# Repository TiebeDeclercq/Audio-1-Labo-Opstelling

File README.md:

# Audio1-Labo-Opstelling

Complete printplaat met alle schakelingen voor audio 1 en vermogenelektronica @Vives kortrijk.
Met een printbare voet voor betere stabiliteit en geen kortsluiting te krijgen.
Op deze voet wordt er gewerkt met heated inserts (M3) voor het monteren van de print.

De printplaat bevat een Klasse A versterker in twee-traps configuratie met Darlington uitgang. Daarnaast is er een Klasse AB versterker met push-pull configuratie en diode bias die werkt op dual supply spanning.
Voor frequentie-analyse zijn er twee circuits: een BJT common emitter configuratie en een JFET common source configuratie, beide met bypass mogelijkheden. Alle belangrijke signalen zijn toegankelijk via testpunten en connectors.

Het schema is als volgt:

Voor het solderen kan je gebruikmaken van de meegeleverde BOM file, de printplaat is een mix van SMD en TH componenten.

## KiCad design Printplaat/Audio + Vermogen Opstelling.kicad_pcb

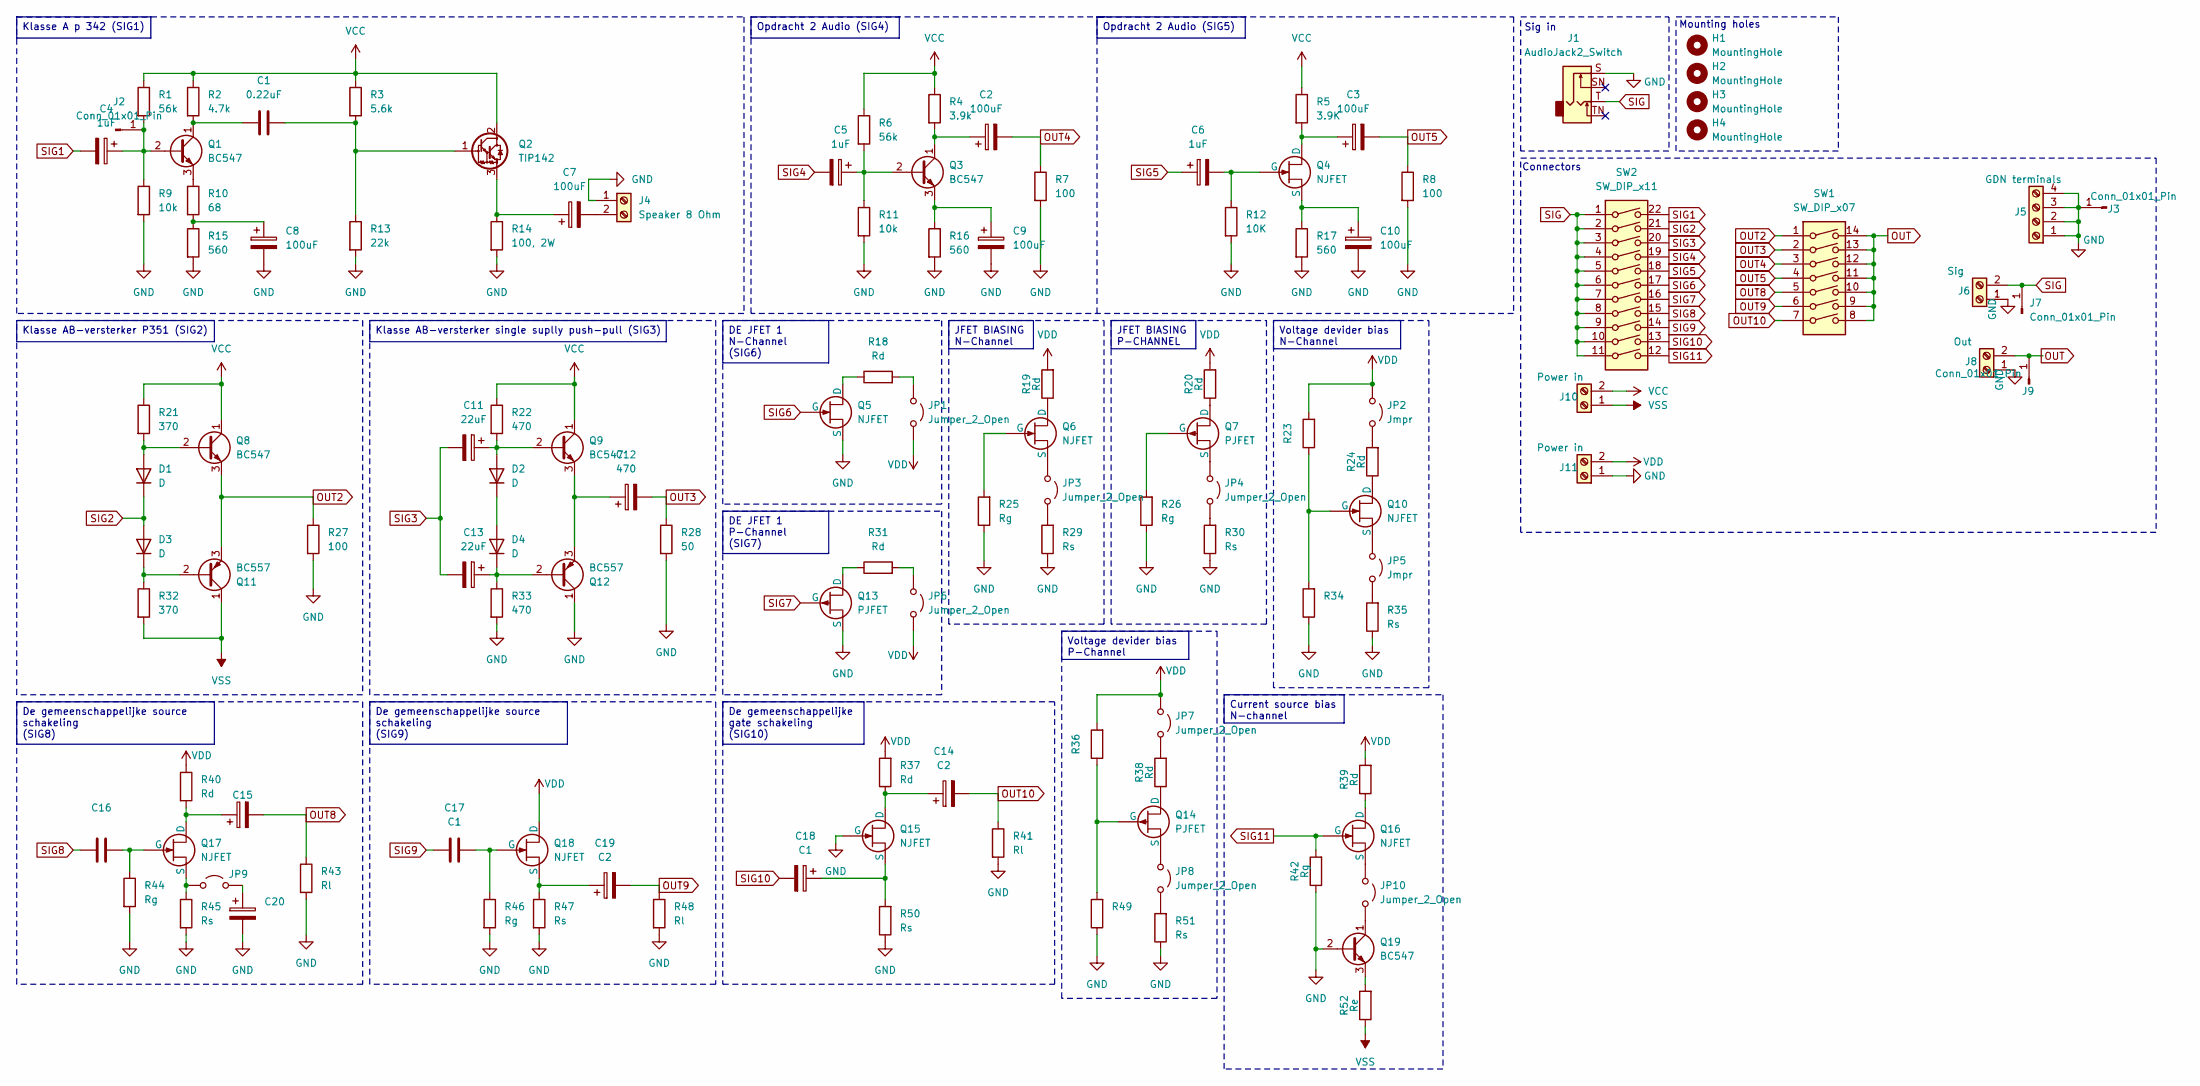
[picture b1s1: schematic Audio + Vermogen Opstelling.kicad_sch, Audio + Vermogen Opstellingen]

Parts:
C1: 0.22uF; C_0805_2012Metric
C2, C3, C9, C10: 100uF; CP_Axial_L11.0mm_D5.0mm_P18.00mm_Horizontal
C4: 1uF; CP_Elec_4x5.4
C5, C6: 1uF; CP_Axial_L11.0mm_D5.0mm_P18.00mm_Horizontal
C7, C8: 100uF; CP_Elec_6.3x5.4
C11, C13: 22uF; CP_Axial_L11.0mm_D5.0mm_P18.00mm_Horizontal
C12: 470; CP_Axial_L11.0mm_D5.0mm_P18.00mm_Horizontal
C14, C19: C2; CP_Axial_L11.0mm_D5.0mm_P18.00mm_Horizontal
C15, C16, C20: CP_Axial_L11.0mm_D5.0mm_P18.00mm_Horizontal
C17, C18: C1; CP_Axial_L11.0mm_D5.0mm_P18.00mm_Horizontal
D1, D2, D3, D4: D; D_DO-15_P15.24mm_Horizontal
H1, H2, H3, H4: MountingHole; MountingHole_3.2mm_M3
J1: AudioJack2_Switch; Jack_3.5mm_KoreanHropartsElec_PJ-320D-4A_Horizontal
J2, J3, J7, J9: Conn_01x01_Pin; PinHeader_1x01_P2.54mm_Vertical
J4: Speaker 8 Ohm; TerminalBlock_Phoenix_MKDS-1,5-2_1x02_P5.00mm_Horizontal
J5: GDN terminals; TerminalBlock_Phoenix_MKDS-1,5-4-5.08_1x04_P5.08mm_Horizont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
J6: Sig; TerminalBlock_Phoenix_MKDS-1,5-2_1x02_P5.00mm_Horizontal
J8: Out; TerminalBlock_Phoenix_MKDS-1,5-2_1x02_P5.00mm_Horizontal
J10, J11: Power in; TerminalBlock_Phoenix_MKDS-1,5-2_1x02_P5.00mm_Horizontal
JP1, JP3, JP4, JP6, JP7, JP8, JP10: Jumper_2_Open; PinHeader_1x02_P2.54mm_Vertical
JP2, JP5: Jmpr; PinHeader_1x02_P2.54mm_Vertical
JP9: PinHeader_1x02_P2.54mm_Vertical
Q1, Q3, Q8, Q9, Q19: BC547; TO-92_Inline
Q2: TIP142; TO-220-3_Horizontal_TabDown
Q4, Q5, Q6, Q10, Q15, Q16, Q17, Q18: NJFET; TRANS_J109
Q7, Q13, Q14: PJFET; SOT23
Q11, Q12: BC557; TO-92_Inline
R1: 56k; R_0805_2012Metric_Pad1.20x1.40mm_HandSolder
R2: 4.7k; R_0805_2012Metric_Pad1.20x1.40mm_HandSolder
R3: 5.6k; R_0805_2012Metric_Pad1.20x1.40mm_HandSolder
R4: 3.9k; R_Axial_DIN0207_L6.3mm_D2.5mm_P10.16mm_Horizontal
R5: 3.9K; R_Axial_DIN0207_L6.3mm_D2.5mm_P10.16mm_Horizontal
R6: 56k; R_Axial_DIN0207_L6.3mm_D2.5mm_P10.16mm_Horizontal
R7, R8, R27: 100; R_Axial_DIN0207_L6.3mm_D2.5mm_P10.16mm_Horizontal
R9: 10k; R_0805_2012Metric_Pad1.20x1.40mm_HandSolder
R10: 68; R_0805_2012Metric_Pad1.20x1.40mm_HandSolder
R11: 10k; R_Axial_DIN0207_L6.3mm_D2.5mm_P10.16mm_Horizontal
R12: 10K; R_Axial_DIN0207_L6.3mm_D2.5mm_P10.16mm_Horizontal
R13: 22k; R_0805_2012Metric_Pad1.20x1.40mm_HandSolder
R14: 100, 2W; R_2512_6332Metric_Pad1.40x3.35mm_HandSolder
R15: 560; R_0805_2012Metric_Pad1.20x1.40mm_HandSolder
R16, R17: 560; R_Axial_DIN0207_L6.3mm_D2.5mm_P10.16mm_Horizontal
R18, R19, R20, R24, R31, R37, R38, R39, R40: Rd; R_Axial_DIN0207_L6.3mm_D2.5mm_P10.16mm_Horizontal
R21, R32: 370; R_Axial_DIN0207_L6.3mm_D2.5mm_P10.16mm_Horizontal
R22, R33: 470; R_Axial_DIN0207_L6.3mm_D2.5mm_P10.16mm_Horizontal
R23, R34, R36, R49: R_Axial_DIN0207_L6.3mm_D2.5mm_P10.16mm_Horizontal
R25, R26, R42, R44, R46: Rg; R_Axial_DIN0207_L6.3mm_D2.5mm_P10.16mm_Horizontal
R28: 50; R_Axial_DIN0207_L6.3mm_D2.5mm_P10.16mm_Horizontal
R29, R30, R35, R45, R47, R50, R51: Rs; R_Axial_DIN0207_L6.3mm_D2.5mm_P10.16mm_Horizontal
R41, R43, R48: Rl; R_Axial_DIN0207_L6.3mm_D2.5mm_P10.16mm_Horizontal
R52: Re; R_Axial_DIN0207_L6.3mm_D2.5mm_P10.16mm_Horizontal
SW1: SW_DIP_x07; SW_DIP_SPSTx07_Slide_9.78x19.96mm_W7.62mm_P2.54mm
SW2: SW_DIP_x11; SW_DIP_SPSTx11_Slide_9.78x30.12mm_W7.62mm_P2.54mm

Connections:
GND: C8.2, C9.2, C10.2, C20.2, J1.S, J3.1, J4.1, J5.1, J5.2, J5.3, J5.4, J6.1, J8.1, J11.1, Q5.3 (S), Q12.1 (C), Q13.3 (S), Q15.2 (G), Q19.2 (B), R7.2, R8.2, R9.2, R11.2, R12.2, R13.2, R14.2, R15.2, R16.2, R17.2, R25.1, R26.1, R27.2, R28.2, R29.1, R30.1, R33.2, R34.1, R35.1, R41.2, R42.1, R43.2, R44.2, R45.2, R46.2, R47.2, R48.2, R49.1, R50.1, R51.1
unnamed: C8.1, R10.2, R15.1
unnamed: D1.2 (A), Q8.2 (B), R21.2
unnamed: C11.1, D2.2 (A), Q9.2 (B), R22.2
unnamed: D2.1 (K), D4.2 (A)
unnamed: D3.1 (K), Q11.2 (B), R32.1
unnamed: C13.1, D4.1 (K), Q12.2 (B), R33.1
unnamed: C4.1, J2.1, Q1.2 (B), R1.2, R9.1
unnamed: C7.2, J4.2
unnamed: JP1.1 (A), R18.2
unnamed: JP2.2 (B), R24.2
unnamed: JP3.1 (A), Q6.3 (S)
unnamed: JP3.2 (B), R29.2
unnamed: JP4.1 (A), Q7.3 (S)
unnamed: JP4.2 (B), R30.2
unnamed: JP5.1 (A), Q10.3 (S)
unnamed: JP5.2 (B), R35.2
unnamed: JP6.1 (A), R31.2
unnamed: JP7.2 (B), R38.2
unnamed: JP8.1 (A), Q14.3 (S)
unnamed: JP8.2 (B), R51.2
unnamed: JP9.1 (A), Q17.3 (S), R45.1
unnamed: C20.1, JP9.2 (B)
unnamed: JP10.1 (A), Q16.3 (S)
unnamed: JP10.2 (B), Q19.1 (C)
unnamed: C1.1, Q1.1 (C), R2.2
unnamed: Q1.3 (E), R10.1
unnamed: C1.2, Q2.1 (B), R3.2, R13.1
unnamed: C7.1, Q2.3 (E), R14.1
unnamed: C5.1, Q3.2 (B), R6.2, R11.1
unnamed: C2.1, Q3.1 (C), R4.2
unnamed: C9.1, Q3.3 (E), R16.1
unnamed: C3.1, Q4.1 (D), R5.2
unnamed: C6.2, Q4.2 (G), R12.1
unnamed: C10.1, Q4.3 (S), R17.1
unnamed: Q5.1 (D), R18.1
unnamed: Q6.1 (D), R19.1
unnamed: Q6.2 (G), R25.2
unnamed: Q7.1 (D), R20.1
unnamed: Q7.2 (G), R26.2
unnamed: Q10.1 (D), R24.1
unnamed: Q10.2 (G), R23.1, R34.2
unnamed: C12.1, Q9.3 (E), Q12.3 (E)
unnamed: Q13.1 (D), R31.1
unnamed: Q14.1 (D), R38.1
unnamed: Q14.2 (G), R36.1, R49.2
unnamed: C14.1, Q15.1 (D), R37.1
unnamed: C18.1, Q15.3 (S), R50.2
unnamed: Q16.1 (D), R39.1
unnamed: C15.1, Q17.1 (D), R40.2
unnamed: C16.2, Q17.2 (G), R44.1
unnamed: C17.2, Q18.2 (G), R46.1
unnamed: C19.1, Q18.3 (S), R47.1
unnamed: Q19.3 (E), R52.2
OUT: J8.2, J9.1, SW1.8, SW1.9, SW1.10, SW1.11, SW1.12, SW1.13, SW1.14
OUT2: Q8.3 (E), Q11.3 (E), R27.1, SW1.1
OUT3: C12.2, R28.1, SW1.2
OUT4: C2.2, R7.1, SW1.3
OUT5: C3.2, R8.1, SW1.4
OUT8: C15.2, R43.1, SW1.5
OUT9: C19.2, R48.1, SW1.6
OUT10: C14.2, R41.1, SW1.7
SIG: J1.T, J6.2, J7.1, SW2.1, SW2.2, SW2.3, SW2.4, SW2.5, SW2.6, SW2.7, SW2.8, SW2.9, SW2.10, SW2.11
SIG1: C4.2, SW2.22
SIG2: D1.1 (K), D3.2 (A), SW2.21
SIG3: C11.2, C13.2, SW2.20
SIG4: C5.2, SW2.19
SIG5: C6.1, SW2.18
SIG6: Q5.2 (G), SW2.17
SIG7: Q13.2 (G), SW2.16
SIG8: C16.1, SW2.15
SIG9: C17.1, SW2.14
SIG10: C18.2, SW2.13
SIG11: Q16.2 (G), R42.2, SW2.12
VCC: J10.2, Q2.2 (C), Q8.1 (C), Q9.1 (C), R1.1, R2.1, R3.1, R4.1, R5.1, R6.1, R21.1, R22.1
VDD: J11.2, JP1.2 (B), JP2.1 (A), JP6.2 (B), JP7.1 (A), Q18.1 (D), R19.2, R20.2, R23.2, R36.2, R37.2, R39.2, R40.1
VSS: J10.1, Q11.1 (C), R32.2, R52.1

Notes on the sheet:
Sig in
Connectors
Mounting holes
DE JFET 1 N-Channel (SIG6)
Klasse AB-versterker single suplly push-pull (SIG3)
De gemeenschappelijke source schakeling (SIG9)
Current source bias N-channel
DE JFET 1 P-Channel (SIG7)
Opdracht 2 Audio (SIG5)
Opdracht 2 Audio (SIG4)
Klasse AB-versterker P351 (SIG2)
De gemeenschappelijke source schakeling (SIG8)
JFET BIASING N-Channel
Voltage devider bias N-Channel
Voltage devider bias P-Channel
Klasse A p 342 (SIG1)
JFET BIASING P-CHANNEL
De gemeenschappelijke gate schakeling (SIG10)

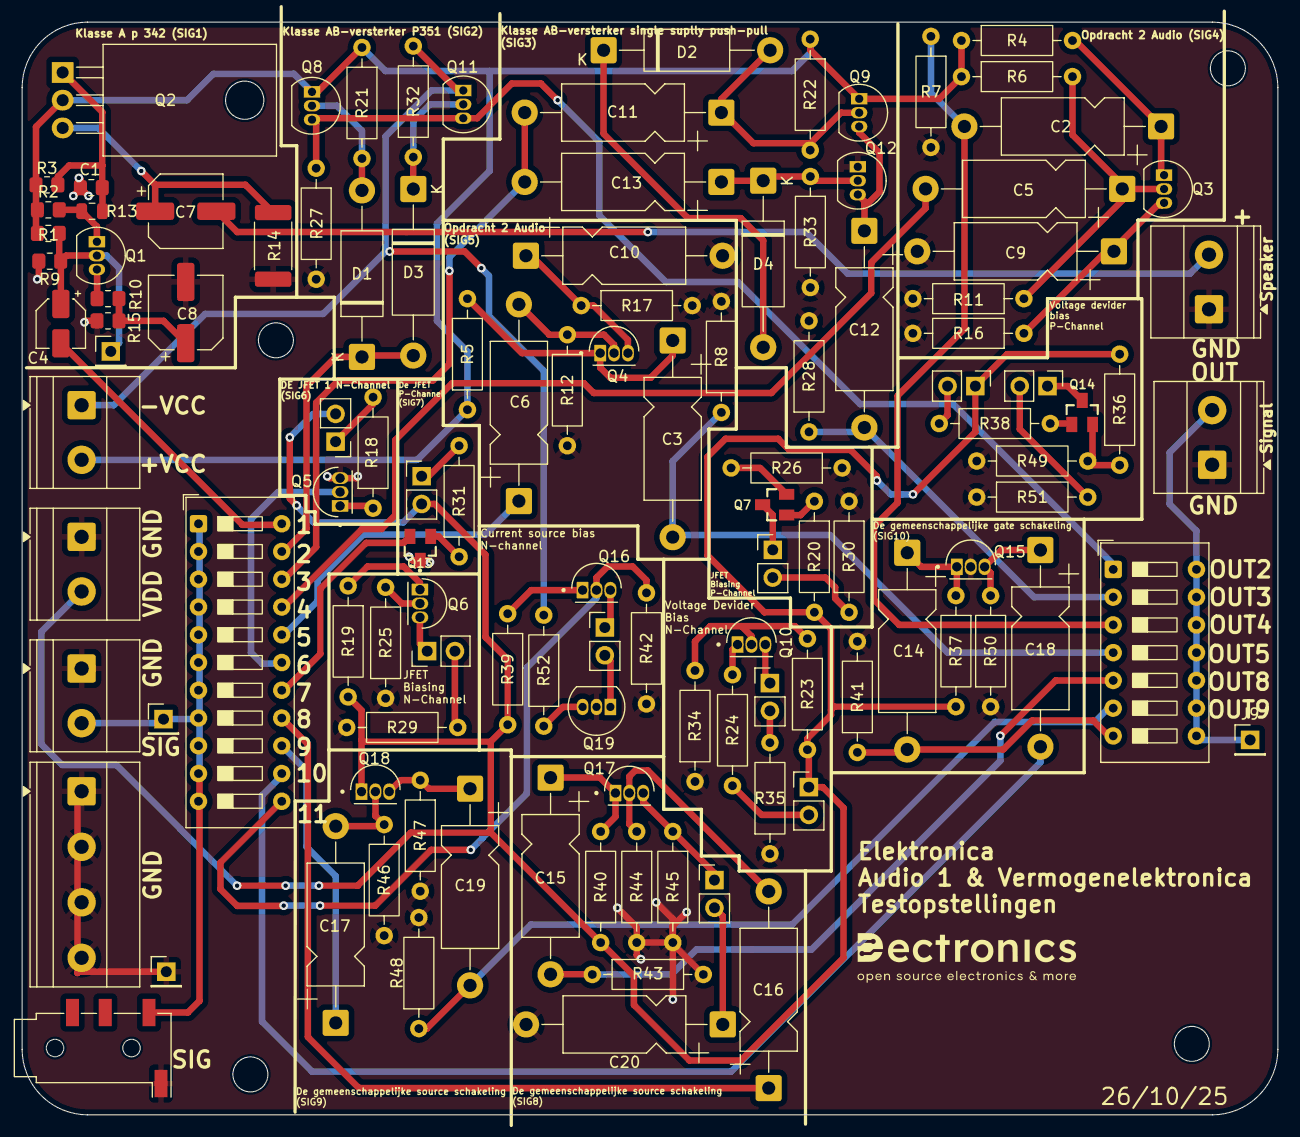
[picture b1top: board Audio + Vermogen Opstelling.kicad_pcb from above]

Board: 2 copper layers, 114.9 x 100.0 mm, 122 parts (0 on the bottom side), 77 nets.

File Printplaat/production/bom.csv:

Designator,Footprint,Quantity,Value,LCSC Part #
C1,0805,1,0.22uF,
"C10, C15, C16, C2, C20, C3, C5, C6, C9",CP_Axial_L11.0mm_D5.0mm_P18.00mm_Horizontal,9,~,
"C11, C13",CP_Axial_L11.0mm_D5.0mm_P18.00mm_Horizontal,2,22uF,
C12,CP_Axial_L11.0mm_D5.0mm_P18.00mm_Horizontal,1,470,
"C14, C19",CP_Axial_L11.0mm_D5.0mm_P18.00mm_Horizontal,2,C2,
"C17, C18",CP_Axial_L11.0mm_D5.0mm_P18.00mm_Horizontal,2,C1,
C4,CP_Elec_4x5.4,1,1uF,
"C7, C8",CP_Elec_6.3x5.4,2,100uF,
"D1, D2, D3, D4",D_DO-15_P15.24mm_Horizontal,4,D,
J1,Jack_3.5mm_KoreanHropartsElec_PJ-320D-4A_Horizontal,1,AudioJack2_Switch,
"J10, J11","TerminalBlock_Phoenix_MKDS-1,5-2_1x02_P5.00mm_Horizontal",2,Power in,
"J2, J3, J7, J9",PinHeader_1x01_P2.54mm_Vertical,4,Conn_01x01_Pin,
J4,"TerminalBlock_Phoenix_MKDS-1,5-2_1x02_P5.00mm_Horizontal",1,Speaker 8 Ohm,
J5,"TerminalBlock_Phoenix_MKDS-1,5-4-5.08_1x04_P5.08mm_Horizontal",1,GDN terminals,
J6,"TerminalBlock_Phoenix_MKDS-1,5-2_1x02_P5.00mm_Horizontal",1,Sig,
J8,"TerminalBlock_Phoenix_MKDS-1,5-2_1x02_P5.00mm_Horizontal",1,Out,
"JP1, JP10, JP3, JP4, JP6, JP7, JP8",PinHeader_1x02_P2.54mm_Vertical,7,Jumper_2_Open,
"JP2, JP5",PinHeader_1x02_P2.54mm_Vertical,2,Jmpr,
JP9,PinHeader_1x02_P2.54mm_Vertical,1,~,
"Q1, Q19, Q3, Q8, Q9",TO-92_Inline,5,BC547,
"Q10, Q15, Q16, Q17, Q18, Q4, Q5, Q6",TRANS_J109,8,NJFET,
"Q11, Q12",TO-92_Inline,2,BC557,
"Q13, Q14, Q7",SOT23,3,PJFET,
Q2,TO-220-3_Horizontal_TabDown,1,TIP142,
R1,0805,1,56k,
R10,0805,1,68,
"R11, R23, R34, R36, R49, R6",R_Axial_DIN0207_L6.3mm_D2.5mm_P10.16mm_Horizontal,6,~,
"R12, R25, R26, R42, R44, R46",R_Axial_DIN0207_L6.3mm_D2.5mm_P10.16mm_Horizontal,6,Rg,
R13,0805,1,22k,
R14,2512,1,"33, 2W",
R15,0805,1,560,
"R16, R52",R_Axial_DIN0207_L6.3mm_D2.5mm_P10.16mm_Horizontal,2,Re,
"R17, R29, R30, R35, R45, R47, R50, R51",R_Axial_DIN0207_L6.3mm_D2.5mm_P10.16mm_Horizontal,8,Rs,
"R18, R19, R20, R24, R31, R37, R38, R39, R40, R5",R_Axial_DIN0207_L6.3mm_D2.5mm_P10.16mm_Horizontal,10,Rd,
R2,0805,1,4.7k,
"R21, R32",R_Axial_DIN0207_L6.3mm_D2.5mm_P10.16mm_Horizontal,2,430,
"R22, R33",R_Axial_DIN0207_L6.3mm_D2.5mm_P10.16mm_Horizontal,2,470,
R27,R_Axial_DIN0207_L6.3mm_D2.5mm_P10.16mm_Horizontal,1,16,
R28,R_Axial_DIN0207_L6.3mm_D2.5mm_P10.16mm_Horizontal,1,50,
R3,0805,1,5.6k,
R4,R_Axial_DIN0207_L6.3mm_D2.5mm_P10.16mm_Horizontal,1,Rc,
"R41, R43, R48, R7, R8",R_Axial_DIN0207_L6.3mm_D2.5mm_P10.16mm_Horizontal,5,Rl,
R9,0805,1,10k,
SW1,SW_DIP_SPSTx07_Slide_9.78x19.96mm_W7.62mm_P2.54mm,1,SW_DIP_x07,
SW2,SW_DIP_SPSTx11_Slide_9.78x30.12mm_W7.62mm_P2.54mm,1,SW_DIP_x11,

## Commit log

2025-12-31 init
2025-12-31 Fix formatting in README description
